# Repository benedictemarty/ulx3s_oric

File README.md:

# ulx3s_oric — Oric Atmos sur FPGA ULX3S

Portage matériel (core FPGA) de l'**Oric Atmos** pour la carte **ULX3S** (Lattice ECP5-85F),
entièrement en Verilog et synthétisable avec la chaîne open-source (yosys / nextpnr-ecp5).

La référence fonctionnelle est l'émulateur logiciel `~/Oric1` (timing ULA, VIA, clavier, AY
vérifiés contre son code source).

## Fonctionnalités (v1)

- CPU **6502** à 1 MHz (core Arlet Ottens)
- **ULA** vidéo réimplémentée : timing PAL 50 Hz (64 µs/ligne, 312 lignes), modes
  TEXT 40×28 et HIRES 240×200, attributs série (ink/paper/charset alternatif/double
  hauteur/clignotement/inversion), palette 8 couleurs
- ROM **BASIC 1.1b** (Atmos), 48 Ko de RAM
- **VIA 6522** complète ($0300) : ports A/B, timers T1/T2, IFR/IER, PCR/ACR
- **AY-3-8912** (core jt49) piloté par CA2/CB2 (BC1/BDIR), audio sur la prise jack
  (DAC 4 bits ULX3S)
- **Clavier USB** sur le port US2 (core usb_hid_host), traduit vers la matrice 8×8 Oric
- Sortie vidéo **HDMI/DVI** (GPDI) 640×480@60, framebuffer 240×224 doublé ×2

## Arborescence

```
rtl/           RTL spécifique au projet (ULA, VIA, clavier, top…)
third_party/   Cores libres vendorés (verilog-6502, jt49, usb_hid_host)
roms/          ROM BASIC 1.1b (+ conversion .hex pour $readmemh)
sim/           Testbenches iverilog
tests/         Scripts de test automatisés
constraints/   Fichier LPF ULX3S v2.0 (85F)
docs/          Documentation projet (architecture, backlog agile)
build/         Produits de synthèse (non versionnés)
```

## ROMs requises (non fournies)

Les ROMs propriétaires ne sont **pas distribuées** dans ce dépôt (copyright). À
placer soi-même dans `roms/` avant de construire :

| Fichier | Contenu | Format |
|---------|---------|--------|
| `roms/basic11b.rom` | BASIC 1.1b (Atmos), 16 Ko | binaire |
| `roms/basic11b.hex` | idem, converti pour `$readmemh` | un octet hexa/ligne |
| `roms/basic10.hex`  | BASIC 1.0 (banque alternative) | idem |
| `roms/microdis.hex` | firmware Microdisc (support `.dsk`) | idem |

Conversion binaire → `.hex` (exemple) :
```sh
xxd -c1 -p roms/basic11b.rom > roms/basic11b.hex
```
`roms/font8x8.hex` (police OSD, maison) est fournie.

## Construire

```sh
make            # synthèse complète -> build/oric_ulx3s.bit
make test       # lance tous les testbenches (iverilog)
make prog       # flash SRAM via openFPGALoader (ou: make prog-fujprog)
```

## Matériel requis

- ULX3S avec ECP5-**85F**
- Écran HDMI (640×480@60 minimum)
- Clavier USB (le port **US2**, connecteur micro-USB du dessus)
- Casque/enceintes sur la prise jack 3,5 mm (son AY)

## Licences

- `third_party/verilog-6502` : licence libre (voir README amont, Arlet Ottens)
- `third_party/jt49` : GPL-3.0 (Jose Tejada)
- `third_party/usb_hid_host` : MIT (nand2mario)
- RTL du projet : GPL-3.0 (contaminé par jt49)
- Les ROMs BASIC (Oric/Tangerine) et le firmware Microdisc restent la propriété
  de leurs ayants droit ; **non distribués ici** — à fournir localement (cf.
  « ROMs requises »).

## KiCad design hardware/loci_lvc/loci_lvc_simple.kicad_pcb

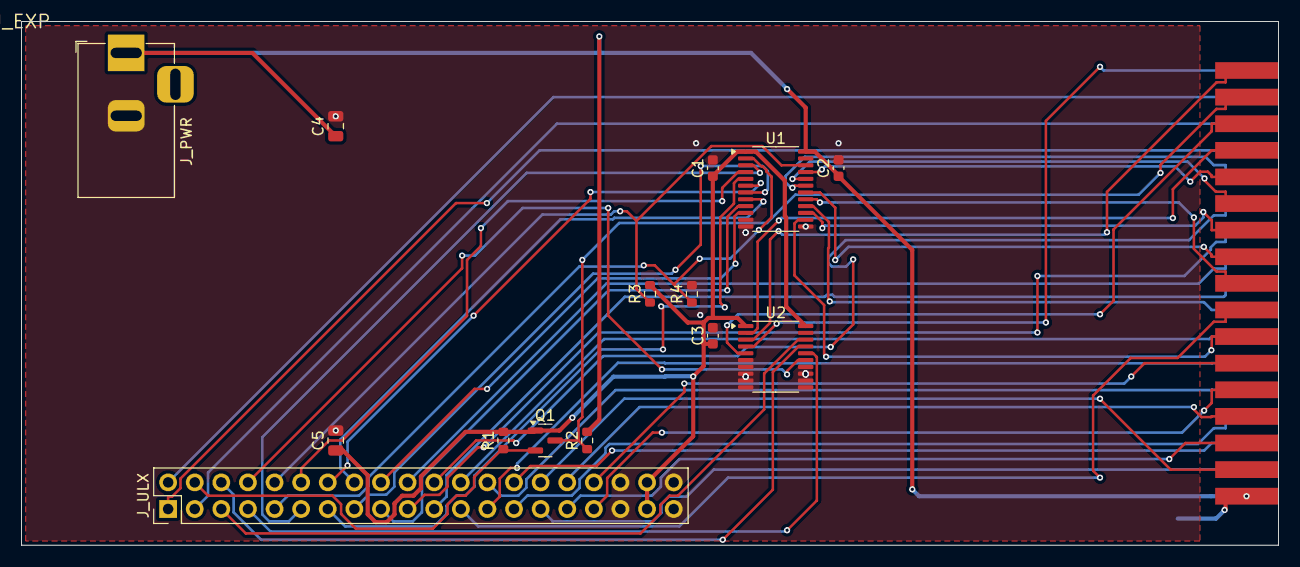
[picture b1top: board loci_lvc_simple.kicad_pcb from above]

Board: 2 copper layers, 120.0 x 50.0 mm, 15 parts (0 on the bottom side), 50 nets.

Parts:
C1, C2, C3: 100nF; C_0603_1608Metric
C4, C5: 100nF; C_0805_2012Metric
J_EXP: EDGE_34; JEXP_34
J_PWR: Jack_5.5x2.1; BarrelJack_Horizontal
J_ULX: Conn_02x20; PinHeader_2x20_P2.54mm_Vertical
Q1: BSS138; SOT-23
R1, R2, R3, R4: 10k; R_0603_1608Metric
U1: SN74LVCC3245APW; TSSOP-24_4.4x7.8mm_P0.65mm
U2: SN74LVC245APW; TSSOP-20_4.4x6.5mm_P0.65mm

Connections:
+3V3: C1.1, C3.1, C5.1, J_ULX.37, J_ULX.38, Q1.1, R1.2, R3.2, U1.1, U2.1, U2.20
+5V: C2.1, C4.1, J_EXP.33, J_PWR.1, R2.2, U1.24
A0: J_EXP.13, J_ULX.19
A1: J_EXP.15, J_ULX.20
A2: J_EXP.17, J_ULX.21
A3: J_EXP.11, J_ULX.22
A4: J_EXP.20, J_ULX.23
A5: J_EXP.21, J_ULX.24
A6: J_EXP.23, J_ULX.25
A7: J_EXP.25, J_ULX.26
A8: J_EXP.27, J_ULX.27
A9: J_EXP.29, J_ULX.28
A10: J_EXP.31, J_ULX.29
A11: J_EXP.32, J_ULX.30
A12: J_EXP.30, J_ULX.31
A13: J_EXP.28, J_ULX.32
A14: J_EXP.26, J_ULX.33
A15: J_EXP.24, J_ULX.34
D0: J_ULX.11, U1.3
D1: J_ULX.12, U1.4
D2: J_ULX.13, U1.5
D3: J_ULX.14, U1.6
D4: J_ULX.15, U1.7
D5: J_ULX.16, U1.8
D5V0: J_EXP.10, U1.21
D5V1: J_EXP.12, U1.20
D5V2: J_EXP.9, U1.19
D5V3: J_EXP.16, U1.18
D5V4: J_EXP.18, U1.17
D5V5: J_EXP.19, U1.16
D5V6: J_EXP.14, U1.15
D5V7: J_EXP.22, U1.14
D6: J_ULX.17, U1.9
D7: J_ULX.18, U1.10
GND: C1.2, C2.2, C3.2, C4.2, C5.2, J_EXP.34, J_PWR.2, J_ULX.35, J_ULX.36, J_ULX.39, J_ULX.40, R4.2, U1.11, U1.12, U1.13, U2.6, U2.7, U2.8, U2.9, U2.10, U2.11, U2.12, U2.13, U2.14, U2.19
IOCTL5_n: J_EXP.6, U2.5
IOCTL_n: J_ULX.8, U2.15
IO_n: J_EXP.5, J_ULX.3
IRQ5_n: J_EXP.8, U2.2
IRQ_n: J_ULX.5, U2.18
MAP5_n: J_EXP.1, U2.4
MAP_n: J_ULX.7, U2.16
PHI2: J_EXP.3, J_ULX.2
ROMDIS5_n: J_EXP.2, U2.3
ROMDIS_n: J_ULX.6, U2.17
RST5_n: J_EXP.4, Q1.3, R2.1
RST_n: J_ULX.4, Q1.2, R1.1
RW: J_EXP.7, J_ULX.1
XCVR_DIR: J_ULX.9, R4.1, U1.2
XCVR_OE_n: J_ULX.10, R3.1, U1.22

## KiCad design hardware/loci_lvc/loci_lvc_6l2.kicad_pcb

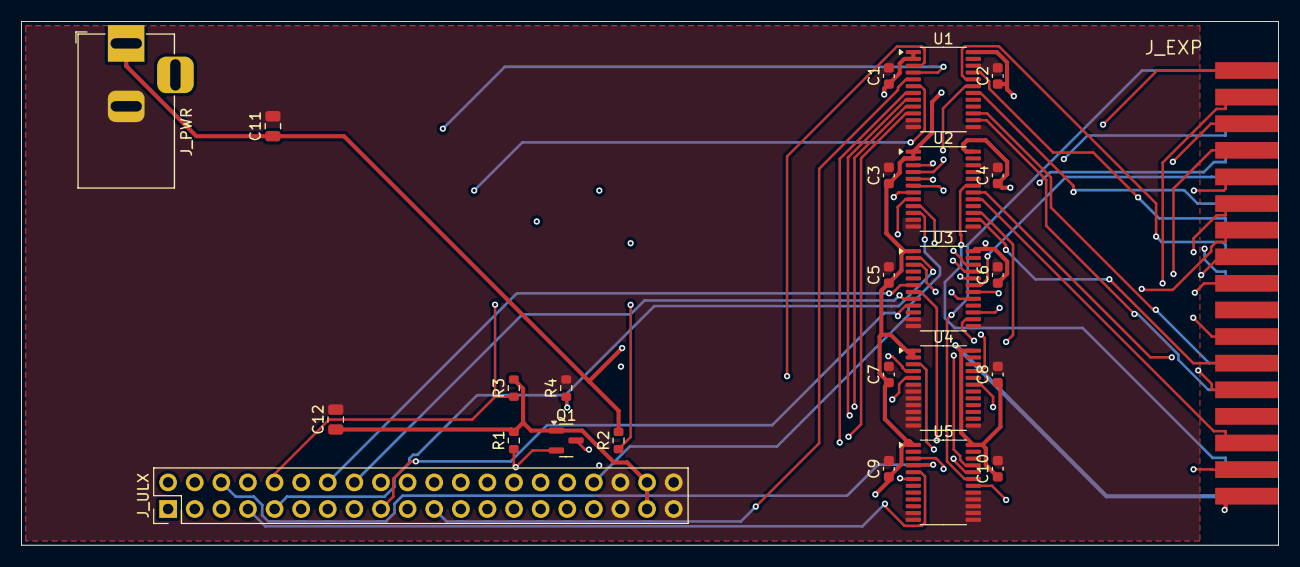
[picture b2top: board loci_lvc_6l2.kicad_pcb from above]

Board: 6 copper layers, 120.0 x 50.0 mm, 25 parts (0 on the bottom side), 69 nets.

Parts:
C1, C2, C3, C4, C5, C6, C7, C8, C9, C10: 100nF; C_0603_1608Metric
C11, C12: 10uF; C_0805_2012Metric
J_EXP: EDGE_34_GOLDFINGERS; JEXP_34_GOLDFINGERS
J_PWR: Jack_5.5x2.1; BarrelJack_Horizontal
J_ULX: Conn_02x20; PinHeader_2x20_P2.54mm_Vertical
Q1: BSS138; SOT-23
R1, R2, R3, R4: 10k; R_0603_1608Metric
U1, U2, U3, U4, U5: SN74LVCC3245APW; TSSOP-24_4.4x7.8mm_P0.65mm

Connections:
+3V3: C1.1, C3.1, C5.1, C7.1, C9.1, C12.1, J_ULX.37, J_ULX.38, Q1.1, R1.2, R3.2, U1.1, U1.2, U2.1, U2.2, U3.1, U4.1, U4.2, U5.1
+5V: C2.1, C4.1, C6.1, C8.1, C10.1, C11.1, J_EXP.33, J_PWR.1, R2.2, U1.24, U2.24, U3.24, U4.24, U5.24
A0: J_ULX.19, U1.3
A1: J_ULX.20, U1.4
A2: J_ULX.21, U1.5
A3: J_ULX.22, U1.6
A4: J_ULX.23, U1.7
A5: J_ULX.24, U1.8
A5V0: J_EXP.13, U1.21
A5V1: J_EXP.15, U1.20
A5V2: J_EXP.17, U1.19
A5V3: J_EXP.11, U1.18
A5V4: J_EXP.20, U1.17
A5V5: J_EXP.21, U1.16
A5V6: J_EXP.23, U1.15
A5V7: J_EXP.25, U1.14
A5V8: J_EXP.27, U2.21
A5V9: J_EXP.29, U2.20
A5V10: J_EXP.31, U2.19
A5V11: J_EXP.32, U2.18
A5V12: J_EXP.30, U2.17
A5V13: J_EXP.28, U2.16
A5V14: J_EXP.26, U2.15
A5V15: J_EXP.24, U2.14
A6: J_ULX.25, U1.9
A7: J_ULX.26, U1.10
A8: J_ULX.27, U2.3
A9: J_ULX.28, U2.4
A10: J_ULX.29, U2.5
A11: J_ULX.30, U2.6
A12: J_ULX.31, U2.7
A13: J_ULX.32, U2.8
A14: J_ULX.33, U2.9
A15: J_ULX.34, U2.10
D0: J_ULX.11, U3.3
D1: J_ULX.12, U3.4
D2: J_ULX.13, U3.5
D3: J_ULX.14, U3.6
D4: J_ULX.15, U3.7
D5: J_ULX.16, U3.8
D5V0: J_EXP.10, U3.21
D5V1: J_EXP.12, U3.20
D5V2: J_EXP.9, U3.19
D5V3: J_EXP.16, U3.18
D5V4: J_EXP.18, U3.17
D5V5: J_EXP.19, U3.16
D5V6: J_EXP.14, U3.15
D5V7: J_EXP.22, U3.14
D6: J_ULX.17, U3.9
D7: J_ULX.18, U3.10
GND: C1.2, C2.2, C3.2, C4.2, C5.2, C6.2, C7.2, C8.2, C9.2, C10.2, C11.2, C12.2, J_EXP.34, J_PWR.2, J_ULX.35, J_ULX.36, J_ULX.39, J_ULX.40, R4.2, U1.11, U1.12, U1.13, U1.22, U2.11, U2.12, U2.13, U2.22, U3.11, U3.12, U3.13, U4.6, U4.7, U4.8, U4.9, U4.10, U4.11, U4.12, U4.13, U4.22, U5.2, U5.11, U5.12, U5.13, U5.14, U5.15, U5.16, U5.17, U5.22
IO5_n: J_EXP.5, U4.19
IOCTL5_n: J_EXP.6, U5.18
IOCTL_n: J_ULX.8, U5.6
IO_n: J_ULX.3, U4.5
IRQ5_n: J_EXP.8, U5.21
IRQ_n: J_ULX.5, U5.3
MAP5_n: J_EXP.1, U5.19
MAP_n: J_ULX.7, U5.5
PHI2: J_ULX.2, U4.4
PHI2_5: J_EXP.3, U4.20
ROMDIS5_n: J_EXP.2, U5.20
ROMDIS_n: J_ULX.6, U5.4
RST5_n: J_EXP.4, Q1.3, R2.1
RST_n: J_ULX.4, Q1.2, R1.1
RW: J_ULX.1, U4.3
RW5: J_EXP.7, U4.21
XCVR_DIR: J_ULX.9, R4.1, U3.2
XCVR_OE_n: J_ULX.10, R3.1, U3.22

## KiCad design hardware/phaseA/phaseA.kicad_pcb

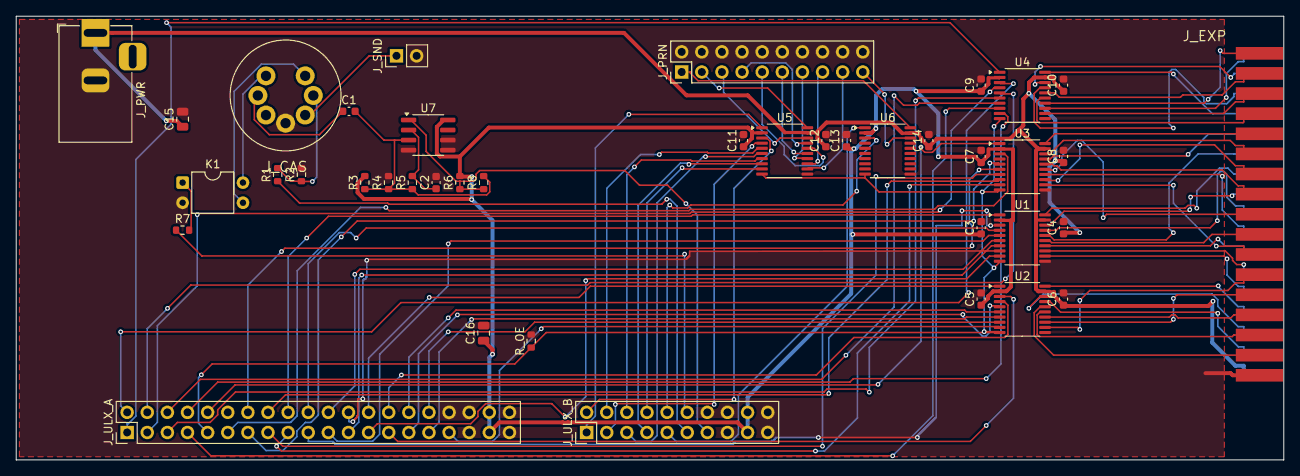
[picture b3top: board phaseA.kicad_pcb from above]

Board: 2 copper layers, 160.0 x 56.0 mm, 40 parts (0 on the bottom side), 99 nets.

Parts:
C1: 1uF; C_0603_1608Metric
C2, C3, C4, C5, C6, C7, C8, C9, C10, C11, C12, C13, C14: 100nF; C_0603_1608Metric
C15, C16: 10uF; C_0805_2012Metric
J_CAS: DIN41524_7pin_270deg_Female
J_EXP: EDGE_34_GOLDFINGERS; JEXP_34_GOLDFINGERS
J_PRN: Conn_02x10; PinHeader_2x10_P2.54mm_Vertical
J_PWR: Jack_5.5x2.1; BarrelJack_Horizontal
J_SND: Conn_01x02; PinHeader_1x02_P2.54mm_Vertical
J_ULX_A: Conn_02x20; PinHeader_2x20_P2.54mm_Vertical
J_ULX_B: Conn_02x10; PinHeader_2x10_P2.54mm_Vertical
K1: AQY212GH; DIP-4_W7.62mm
R1, R6: 10k; R_0603_1608Metric
R2: 1k; R_0603_1608Metric
R3, R4, R5: 100k; R_0603_1608Metric
R7: 470; R_0603_1608Metric
R8: 1M; R_0603_1608Metric
R_OE: 10k; R_0603_1608Metric
U1, U2, U3, U4, U5, U6: TXS0108EPWR; TSSOP-20_4.4x6.5mm_P0.65mm
U7: LM393; SOIC-8_3.9x4.9mm_P1.27mm

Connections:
+3V3: C3.1, C5.1, C7.1, C9.1, C11.1, C13.1, C16.1, J_ULX_A.37, J_ULX_A.38, J_ULX_B.17, J_ULX_B.18, R3.2, R6.2, U1.2, U2.2, U3.2, U4.2, U5.2, U6.2, U7.8
+5V: C4.1, C6.1, C8.1, C10.1, C12.1, C14.1, C15.1, J_EXP.33, J_PWR.1, U1.19, U2.19, U3.19, U4.19, U5.19, U6.19
A0: J_ULX_A.18, U1.1
A1: J_ULX_A.19, U1.3
A2: J_ULX_A.20, U1.4
A3: J_ULX_A.21, U1.5
A4: J_ULX_A.22, U1.6
A5: J_ULX_A.23, U1.7
A5V0: J_EXP.13, U1.20
A5V1: J_EXP.15, U1.18
A5V2: J_EXP.17, U1.17
A5V3: J_EXP.11, U1.16
A5V4: J_EXP.20, U1.15
A5V5: J_EXP.21, U1.14
A5V6: J_EXP.23, U1.13
A5V7: J_EXP.25, U1.12
A5V8: J_EXP.27, U2.20
A5V9: J_EXP.29, U2.18
A5V10: J_EXP.31, U2.17
A5V11: J_EXP.32, U2.16
A5V12: J_EXP.30, U2.15
A5V13: J_EXP.28, U2.14
A5V14: J_EXP.26, U2.13
A5V15: J_EXP.24, U2.12
A6: J_ULX_A.24, U1.8
A7: J_ULX_A.25, U1.9
A8: J_ULX_A.26, U2.1
A9: J_ULX_A.27, U2.3
A10: J_ULX_A.28, U2.4
A11: J_ULX_A.29, U2.5
A12: J_ULX_A.30, U2.6
A13: J_ULX_A.31, U2.7
A14: J_ULX_A.32, U2.8
A15: J_ULX_A.33, U2.9
ACK: J_ULX_B.10, U6.3
D0: J_ULX_A.10, U3.1
D1: J_ULX_A.11, U3.3
D2: J_ULX_A.12, U3.4
D3: J_ULX_A.13, U3.5
D4: J_ULX_A.14, U3.6
D5: J_ULX_A.15, U3.7
D5V0: J_EXP.10, U3.20
D5V1: J_EXP.12, U3.18
D5V2: J_EXP.9, U3.17
D5V3: J_EXP.16, U3.16
D5V4: J_EXP.18, U3.15
D5V5: J_EXP.19, U3.14
D5V6: J_EXP.14, U3.13
D5V7: J_EXP.22, U3.12
D6: J_ULX_A.16, U3.8
D7: J_ULX_A.17, U3.9
GND: C2.2, C3.2, C4.2, C5.2, C6.2, C7.2, C8.2, C9.2, C10.2, C11.2, C12.2, C13.2, C14.2, C15.2, C16.2, J_CAS.2, J_EXP.34, J_PRN.2, J_PRN.4, J_PRN.6, J_PRN.8, J_PRN.10, J_PRN.12, J_PRN.14, J_PRN.16, J_PRN.18, J_PRN.20, J_PWR.2, J_SND.2, J_ULX_A.34, J_ULX_A.35, J_ULX_A.36, J_ULX_A.39, J_ULX_A.40, J_ULX_B.14, J_ULX_B.15, J_ULX_B.16, J_ULX_B.19, J_ULX_B.20, K1.2, R2.2, R4.2, R_OE.2, U1.11, U2.11, U3.11, U4.11, U5.11, U6.11, U7.4, U7.5, U7.6
IN_MINUS: C2.1, R5.2, U7.2
IN_PLUS: C1.2, R3.1, R4.1, R5.1, R8.2, U7.3
IO5_n: J_EXP.5, U4.17
IOCTL5_n: J_EXP.6, U4.12
IOCTL_n: J_ULX_A.8, U4.9
IO_n: J_ULX_A.3, U4.4
IRQ5_n: J_EXP.8, U4.15
IRQ_n: J_ULX_A.5, U4.6
K1_LED_A: K1.1, R7.2
MAP5_n: J_EXP.1, U4.13
MAP_n: J_ULX_A.7, U4.8
MOTOR_3V3: J_ULX_B.12, R7.1
MOTOR_A: J_CAS.6, K1.3
MOTOR_B: J_CAS.7, K1.4
OE_EN: J_ULX_A.9, R_OE.1, U1.10, U2.10, U3.10, U4.10, U5.10, U6.10
PA0: J_ULX_B.1, U5.1
PA1: J_ULX_B.2, U5.3
PA2: J_ULX_B.3, U5.4
PA3: J_ULX_B.4, U5.5
PA4: J_ULX_B.5, U5.6
PA5: J_ULX_B.6, U5.7
PA6: J_ULX_B.7, U5.8
PA7: J_ULX_B.8, U5.9
PHI2: J_ULX_A.2, U4.3
PHI2_5: J_EXP.3, U4.18
PRN_ACK: J_PRN.19, U6.18
PRN_D0: J_PRN.3, U5.20
PRN_D1: J_PRN.5, U5.18
PRN_D2: J_PRN.7, U5.17
PRN_D3: J_PRN.9, U5.16
PRN_D4: J_PRN.11, U5.15
PRN_D5: J_PRN.13, U5.14
PRN_D6: J_PRN.15, U5.13
PRN_D7: J_PRN.17, U5.12
PRN_STB_n: J_PRN.1, U6.20
ROMDIS5_n: J_EXP.2, U4.14
ROMDIS_n: J_ULX_A.6, U4.7
RST5_n: J_EXP.4, U4.16
RST_n: J_ULX_A.4, U4.5
RW: J_ULX_A.1, U4.1
RW5: J_EXP.7, U4.20
SOUND: J_CAS.4, J_SND.1
STROBE_n: J_ULX_B.9, U6.1
TAPE_IN_3V3: J_ULX_B.13, R6.1, R8.1, U7.1
TAPE_IN_DIN: C1.1, J_CAS.3
TAPE_OUT_3V3: J_ULX_B.11, R1.1
TAPE_OUT_DIN: J_CAS.1, R1.2, R2.1

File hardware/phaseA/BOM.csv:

Comment,Designator,Footprint,LCSC Part #
1uF,C1,C_0603_1608Metric,C15849
100nF,"C10,C11,C12,C13,C14,C2,C3,C4,C5,C6,C7,C8,C9",C_0603_1608Metric,C14663
10uF,"C15,C16",C_0805_2012Metric,C15850
DIN41524_7pin_270deg_Female,J_CAS,,TBD
Conn_02x10,"J_PRN,J_ULX_B",PinHeader_2x10_P2.54mm_Vertical,TBD
Jack_5.5x2.1,J_PWR,BarrelJack_Horizontal,TBD
Conn_01x02,J_SND,PinHeader_1x02_P2.54mm_Vertical,TBD
Conn_02x20,J_ULX_A,PinHeader_2x20_P2.54mm_Vertical,TBD
AQY212GH,K1,DIP-4_W7.62mm,TBD
10k,"R1,R6,R_OE",R_0603_1608Metric,C25804
1k,R2,R_0603_1608Metric,C21190
100k,"R3,R4,R5",R_0603_1608Metric,C25803
470,R7,R_0603_1608Metric,C23179
TXS0108EPWR,"U1,U2,U3,U4,U5,U6",TSSOP-20_4.4x6.5mm_P0.65mm,C17206
LM393,U7,SOIC-8_3.9x4.9mm_P1.27mm,C67470

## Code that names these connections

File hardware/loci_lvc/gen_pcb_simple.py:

#!/usr/bin/env python3
# -*- coding: utf-8 -*-
"""gen_pcb_simple.py — Carte adaptateur LOCI, VERSION SIMPLIFIEE (facon LOCI reelle).

Principe : les entrees des peripheriques Oric sont 5 V-tolerantes (seuil TTL ~2 V),
donc les SORTIES du FPGA (A0-A15, PHI2, R/W, /IO) pilotent le peigne EN DIRECT en
3,3 V — aucun transceiver. Seul le bus de donnees (bidirectionnel) a besoin d'un
transceiver, et les entrees de controle (venant du peripherique, 5 V) d'un petit
buffer abaisseur. Resultat : 1x 74LVC4245A + 1x 74LVC245 + 1x BSS138 -> board
peu dense, routable en 2 couches.
"""
import sys, pcbnew
from pcbnew import VECTOR2I, FromMM
FP_LIB = "/usr/share/kicad/footprints"
MM = FromMM

def V(x, y): return VECTOR2I(MM(x), MM(y))

# --- Nets ---
CTRL_FPGA = ["IRQ_n", "ROMDIS_n", "MAP_n", "IOCTL_n"]
CTRL_5V   = ["IRQ5_n", "ROMDIS5_n", "MAP5_n", "IOCTL5_n"]
NET_NAMES = (
    ["GND", "+5V", "+3V3", "XCVR_DIR", "XCVR_OE_n"]
    + ["A%d" % i for i in range(16)]          # adresses : DIRECT FPGA->peigne
    + ["PHI2", "RW", "IO_n"]                    # controle sortie : DIRECT
    + ["D%d" % i for i in range(8)]            # data cote FPGA
    + ["D5V%d" % i for i in range(8)]          # data cote peigne (via U1)
    + CTRL_FPGA + CTRL_5V                       # controle entree (via U2)
    + ["RST_n", "RST5_n"]                       # reset (via Q1)
)

# J_EXP : doigt -> net (numerotation Atmos ; adresses/PHI2/RW/IO = nets directs)
JEXP_NETS = {
    1: "MAP5_n", 2: "ROMDIS5_n", 3: "PHI2", 4: "RST5_n",
    5: "IO_n", 6: "IOCTL5_n", 7: "RW", 8: "IRQ5_n",
    9: "D5V2", 10: "D5V0", 11: "A3", 12: "D5V1",
    13: "A0", 14: "D5V6", 15: "A1", 16: "D5V3",
    17: "A2", 18: "D5V4", 19: "D5V5", 20: "A4",
    21: "A5", 22: "D5V7", 23: "A6", 24: "A15",
    25: "A7", 26: "A14", 27: "A8", 28: "A13",
    29: "A9", 30: "A12", 31: "A10", 32: "A11",
    33: "+5V", 34: "GND",
}

def build_components():
    comps = []
    def add(ref, lib, fp, pos, rot, val, nets):
        comps.append(dict(ref=ref, lib=lib, fp=fp, pos=pos, rot=rot, value=val, nets=nets))

    # U1 = 74LVC4245A (data D0-D7). 1=VCCA 2=DIR 3..10=A1..A8 11/12/13=GND
    # 14..21=B8..B1 22=/OE 24=VCCB. A=FPGA(3V3), B=peigne(5V).
    m1 = {"1": "+3V3", "24": "+5V", "2": "XCVR_DIR", "22": "XCVR_OE_n",
          "11": "GND", "12": "GND", "13": "GND"}
    for i in range(8):                      # A1..A8 = D0..D7
        m1[str(3 + i)] = "D%d" % i
    for i in range(8):                      # B1..B8 = D5V0..D5V7 (pins 21..14)
        m1[str(21 - i)] = "D5V%d" % i
    add("U1", "Package_SO", "TSSOP-24_4.4x7.8mm_P0.65mm", (72, 16), 0,
        "SN74LVCC3245APW", m1)

    # U2 = 74LVC245 (entrees controle, 5V->3V3). alim 3V3, DIR=H (A->B).
    # 1=DIR 2..9=A1..A8 10=GND 11..18=B8..B1 19=/OE 20=VCC.
    m2 = {"1": "+3V3", "20": "+3V3", "10": "GND", "19": "GND"}
    for i in range(4):                      # A1..A4 = IRQ5..IOCTL5 (peigne)
        m2[str(2 + i)] = CTRL_5V[i]
    for i in range(4, 8):                   # A5..A8 inutilises -> GND
        m2[str(2 + i)] = "GND"
    for i in range(4):                      # B1..B4 = IRQ_n..IOCTL_n (pins 18..15)
        m2[str(18 - i)] = CTRL_FPGA[i]
    for i in range(4, 8):                   # B5..B8 inutilises -> GND (pins 14..11)
        m2[str(18 - i)] = "GND"
    add("U2", "Package_SO", "TSSOP-20_4.4x6.5mm_P0.65mm", (72, 32), 0,
        "SN74LVC245APW", m2)

    # Q1 = BSS138 (/RESET drain ouvert) SOT-23 1=G 2=S 3=D
    add("Q1", "Package_TO_SOT_SMD", "SOT-23", (50, 40), 0, "BSS138",
        {"1": "+3V3", "2": "RST_n", "3": "RST5_n"})

    # J_ULX (2x20) cote FPGA
    jux = {}
    for p, n in zip(range(1, 9), ["RW", "PHI2", "IO_n", "RST_n"] + CTRL_FPGA):
        jux[str(p)] = n
    jux["9"] = "XCVR_DIR"; jux["10"] = "XCVR_OE_n"
    for i in range(8): jux[str(11 + i)] = "D%d" % i
    for i in range(16): jux[str(19 + i)] = "A%d" % i
    for p in (35, 36, 39, 40): jux[str(p)] = "GND"
    jux["37"] = "+3V3"; jux["38"] = "+3V3"
    add("J_ULX", "Connector_PinHeader_2.54mm", "PinHeader_2x20_P2.54mm_Vertical",
        (14, 46.54), 90, "Conn_02x20", jux)

    # J_PWR jack 5V
    add("J_PWR", "Connector_BarrelJack", "BarrelJack_Horizontal", (10, 3), 90,
        "Jack_5.5x2.1", {"1": "+5V", "2": "GND"})

    def r(ref, pos, rot, n1, n2):
        add(ref, "Resistor_SMD", "R_0603_1608Metric", pos, rot, "10k", {"1": n1, "2": n2})
    def c(ref, pos, rot, n1, n2, sz="C_0603_1608Metric"):
        add(ref, "Capacitor_SMD", sz, pos, rot, "100nF", {"1": n1, "2": n2})
    r("R1", (46, 40), 90, "RST_n", "+3V3")
    r("R2", (54, 40), 90, "RST5_n", "+5V")
    r("R3", (60, 26), 90, "XCVR_OE_n", "+3V3")
    r("R4", (64, 26), 90, "XCVR_DIR", "GND")
    c("C1", (66, 14), 90, "+3V3", "GND")
    c("C2", (78, 14), 90, "+5V", "GND")
    c("C3", (66, 30), 90, "+3V3", "GND")
    c("C4", (30, 10), 90, "+5V", "GND", "C_0805_2012Metric")
    c("C5", (30, 40), 90, "+3V3", "GND", "C_0805_2012Metric")
    return comps

def make_jexp(board, nets, W):
    fp = pcbnew.FOOTPRINT(board)
    fp.SetFPID(pcbnew.LIB_ID("loci_lvc", "JEXP_34"))
    fp.SetReference("J_EXP"); fp.SetValue("EDGE_34")
    fp.SetAttributes(pcbnew.FP_SMD | pcbnew.FP_EXCLUDE_FROM_BOM
                     | pcbnew.FP_EXCLUDE_FROM_POS_FILES | pcbnew.FP_BOARD_ONLY)
    fp.SetPosition(V(0, 0))
    pitch, fw, fl = 2.54, 1.6, 6.0
    x_edge = W - 0.05; y0 = 25.0 - 8 * pitch
    for k in range(1, 18):
        y = y0 + (k - 1) * pitch
        for num, layer, mask in ((2*k, pcbnew.F_Cu, pcbnew.F_Mask),
                                 (2*k-1, pcbnew.B_Cu, pcbnew.B_Mask)):
            pad = pcbnew.PAD(fp); pad.SetNumber(str(num))
            pad.SetAttribute(pcbnew.PAD_ATTRIB_SMD); pad.SetShape(pcbnew.PAD_SHAPE_RECT)
            pad.SetSize(V(fl, fw)); ls = pcbnew.LSET(); ls.AddLayer(layer); ls.AddLayer(mask)
            pad.SetLayerSet(ls); pad.SetPosition(V(x_edge - fl/2.0, y))
            pad.SetNet(nets[JEXP_NETS[num]]); fp.Add(pad)
    board.Add(fp); return fp

def build(out):
    b = pcbnew.CreateEmptyBoard(); b.SetFileName(out)
    ds = b.GetDesignSettings(); ds.m_CopperEdgeClearance = 0
    ns = ds.m_NetSettings; d = ns.GetDefaultNetclass()
    d.SetTrackWidth(MM(0.25)); d.SetClearance(MM(0.2)); d.SetViaDiameter(MM(0.6)); d.SetViaDrill(MM(0.3))
    pw = pcbnew.NETCLASS("Power")
    pw.SetTrackWidth(MM(0.5)); pw.SetClearance(MM(0.2)); pw.SetViaDiameter(MM(0.6)); pw.SetViaDrill(MM(0.3))
    ns.SetNetclass("Power", pw)
    for p in ("+5V", "+3V3", "GND"): ns.SetNetclassPatternAssignment(p, "Power")
    nets = {}
    for n in NET_NAMES:
        ni = pcbnew.NETINFO_ITEM(b, n); b.Add(ni); nets[n] = ni
    W, H = 120.0, 50.0
    cor = [(0, 0), (W, 0), (W, H), (0, H)]
    for i in range(4):
        s = pcbnew.PCB_SHAPE(b); s.SetShape(pcbnew.SHAPE_T_SEGMENT)
        s.SetStart(V(*cor[i])); s.SetEnd(V(*cor[(i+1) % 4])); s.SetLayer(pcbnew.Edge_Cuts)
        s.SetWidth(MM(0.1)); b.Add(s)
    for comp in build_components():
        fp = pcbnew.FootprintLoad("%s/%s.pretty" % (FP_LIB, comp["lib"]), comp["fp"])
        if fp is None: raise RuntimeError("empreinte introuvable: " + comp["fp"])
        fp.SetReference(comp["ref"]); fp.SetValue(comp["value"])
        fp.SetOrientationDegrees(comp["rot"]); fp.SetPosition(V(*comp["pos"]))
        for pad in fp.Pads():
            n = comp["nets"].get(pad.GetNumber())
            if n: pad.SetNet(nets[n])
        b.Add(fp)
    make_jexp(b, nets, W)
    zpts = [(0.4, 0.4), (W-7.5, 0.4), (W-7.5, H-0.4), (0.4, H-0.4)]
    for layer in (pcbnew.F_Cu, pcbnew.B_Cu):
        z = pcbnew.ZONE(b); z.SetLayer(layer); z.SetNetCode(nets["GND"].GetNetCode())
        z.SetAssignedPriority(0); z.SetLocalClearance(MM(0.3)); z.SetMinThickness(MM(0.25))
        z.SetPadConnection(pcbnew.ZONE_CONNECTION_FULL)
        z.AddPolygon(pcbnew.VECTOR_VECTOR2I([V(x, y) for x, y in zpts]))
        b.Add(z)
    pcbnew.SaveBoard(out, b)
    b2 = pcbnew.LoadBoard(out); pcbnew.ZONE_FILLER(b2).Fill(b2.Zones()); pcbnew.SaveBoard(out, b2)
    print("OK:", out, "| empreintes:", len(b2.GetFootprints()), "| nets:", b2.GetNetCount())

if __name__ == "__main__":
    build(sys.argv[1] if len(sys.argv) > 1 else "loci_lvc_simple.kicad_pcb")
